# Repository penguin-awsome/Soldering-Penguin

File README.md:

# Soldering-Penguin
A Hackclub project where you design a PCB that will do something cool and get it + an eletronics kit. This is not the project, just my submission.

# Slack Username 
Waddle_Penguin

I decided to make my life hell with a penguin who stares at you menacingly and makes your life hell with flashing alternating lights and vibration at certain times of the day. It was cool to make and I think it should work. in the long term, I'm not sure if it actually working would be good for my sleep schedule but oh well.

I cutout the edgecuts with straight lines by hand which was probably not a good way to do it but oh well.

#BOM
- 1x Battery Cell
- 2x 10uf Capacitor
- 2x LED
- 1x DC Motor
- 3x NPN Transistor
- 1x Photoresistor
- 5x 220 Resistor
- 2x 47k Resistor
- 1x Potentiometer

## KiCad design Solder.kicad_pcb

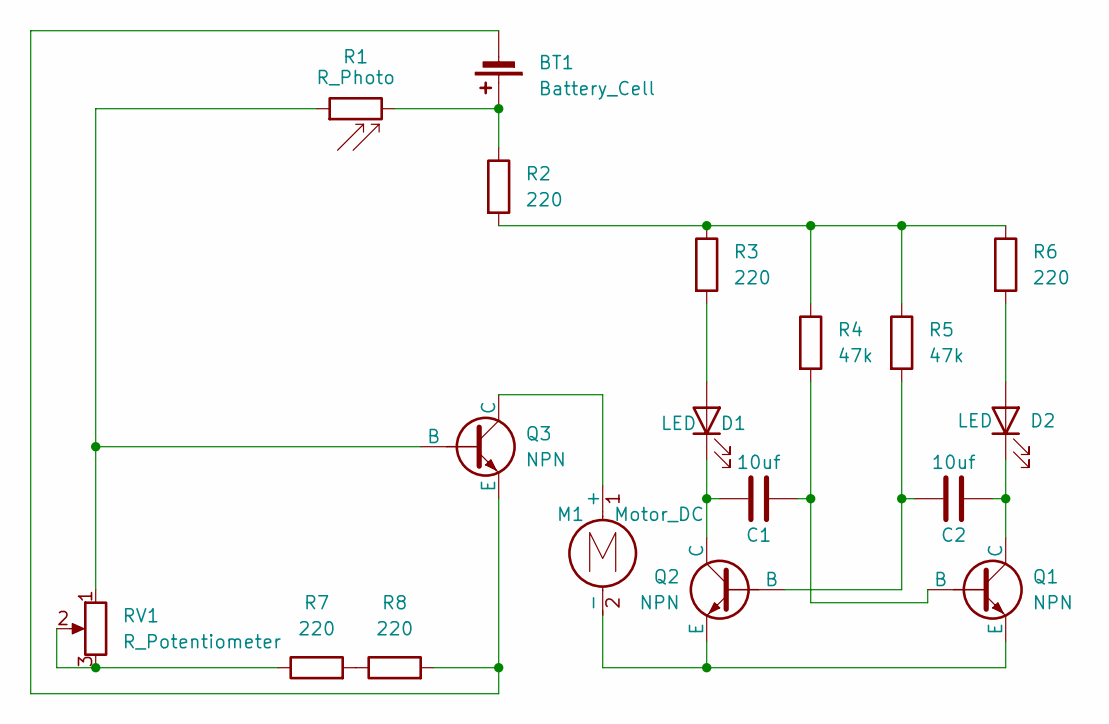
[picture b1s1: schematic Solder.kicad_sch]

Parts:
BT1: Battery_Cell; BatteryHolder_Keystone_3034_1x20mm
C1, C2: 10uf; CP_Radial_D8.0mm_P5.00mm
D1, D2: LED; LED_D5.0mm
M1: Motor_DC; PinHeader_1x02_P2.54mm_Vertical
Q1, Q2, Q3: NPN; TO-92L_HandSolder
R1: R_Photo; R_LDR_5.1x4.3mm_P3.4mm_Vertical
R2, R3, R6, R7, R8: 220; R_Axial_DIN0207_L6.3mm_D2.5mm_P7.62mm_Horizontal
R4, R5: 47k; R_Axial_DIN0207_L6.3mm_D2.5mm_P7.62mm_Horizontal
RV1: R_Potentiometer; Potentiometer_Vishay_T73YP_Vertical

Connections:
unnamed: BT1.1 (+), R1.2, R2.1
unnamed: BT1.2 (-), Q3.3 (E), R8.2
unnamed: D1.2 (A), R3.2
unnamed: C1.1, D1.1 (K), Q2.1 (C)
unnamed: D2.2 (A), R6.2
unnamed: C2.2, D2.1 (K), Q1.1 (C)
unnamed: M1.1 (+), Q3.1 (C)
unnamed: M1.2 (-), Q1.3 (E), Q2.3 (E)
unnamed: C1.2, Q1.2 (B), R4.2
unnamed: C2.1, Q2.2 (B), R5.2
unnamed: Q3.2 (B), R1.1, RV1.1
unnamed: R2.2, R3.1, R4.1, R5.1, R6.1
unnamed: R7.1, RV1.2, RV1.3
unnamed: R7.2, R8.1

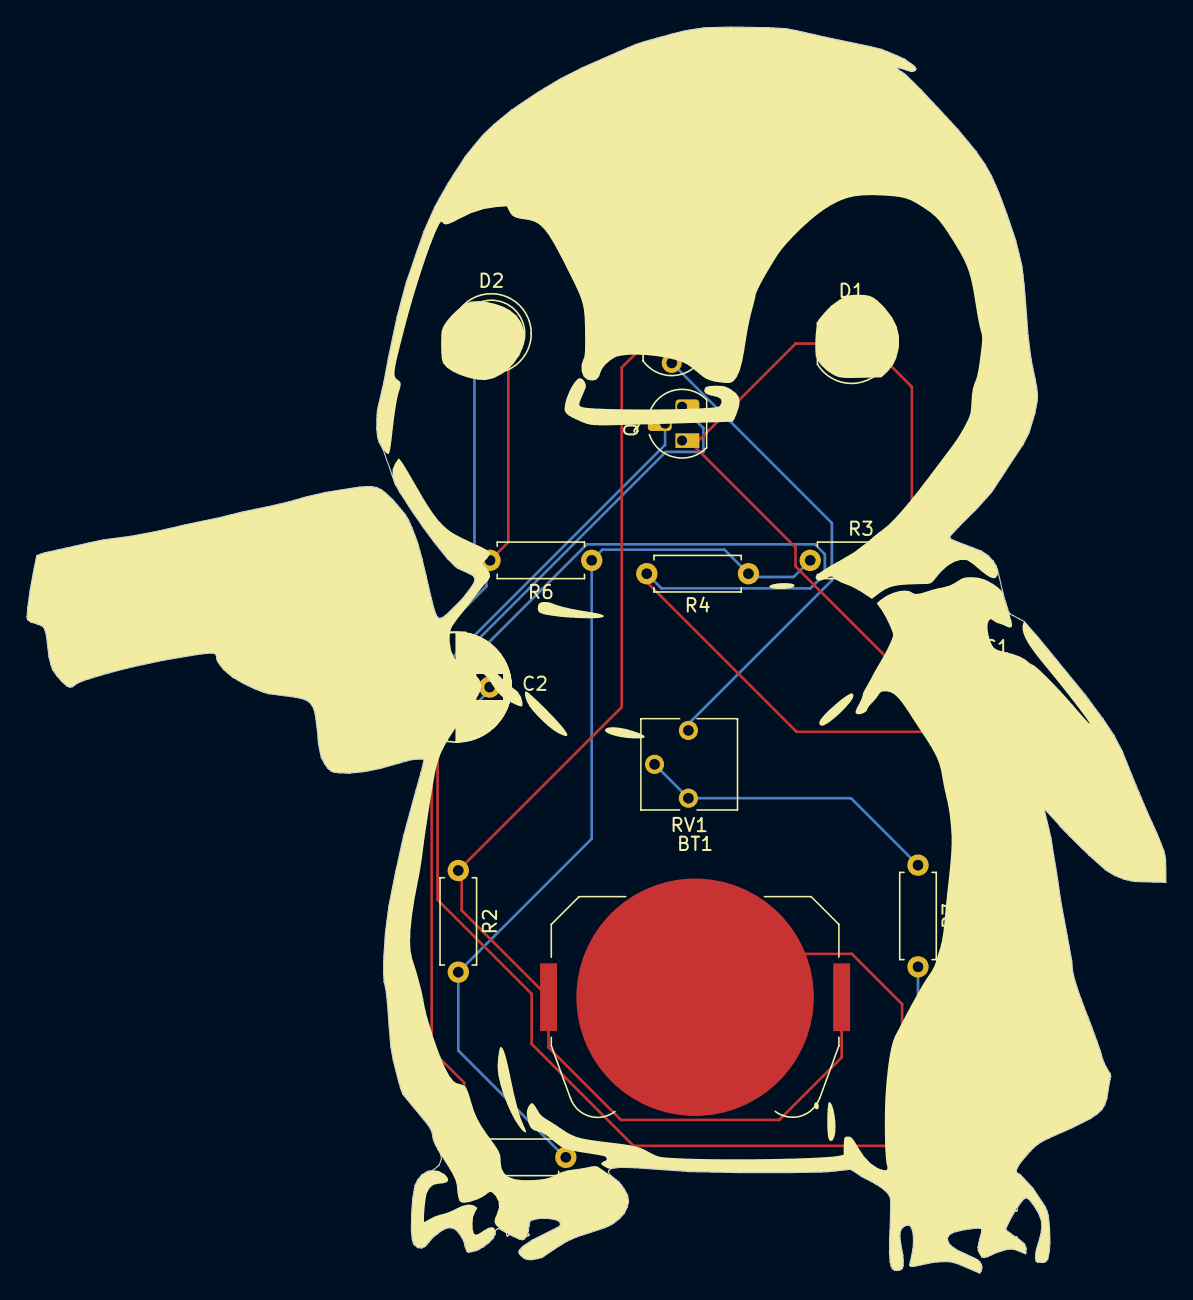
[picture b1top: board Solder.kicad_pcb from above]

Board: 2 copper layers, 85.4 x 93.4 mm, 19 parts (0 on the bottom side), 14 nets.

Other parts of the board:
Penguin_Drawing: LOGO

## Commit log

2025-06-27 Added KiCad Project File
2025-06-27 Added Schematic Photo
